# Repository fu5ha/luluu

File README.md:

# LuLuu!

A cute and smart arm-warmer sleeve with a 1.3" full color TFT display built into the back of the
hand ^_^

## Hardware

Runs on a RaspberryPi RP2040 microcontroller. The small 30x75mm PCB has built-in battery management for a single-cell
LiPo, microSD card storage, and direct connection via SPI to an Adafruit 4520 1.3" TFT (ST7789VW controller). It's
also designed to be expanded via SparkFun Qwiic/Adafruit STEMMA QT compatible (3.3v only) I2C sensor modules. Finallly,
it implements the RaspberryPi 3-wire debug connector spec for ARM SWD serial-wire debugging and RS232-style
UART communication.

The hardware design files all live in the [`hardware/`](hardware/) folder. See the [`README`](hardware/README.md) in
that folder for more.

## Software

The firmware that the LuLuu runs is contained in the [`software/`](software/) folder.
It is written in Rust using some of the amazing Rust embedded tooling.
See the [`README`](software/README.md) in that folder for more.

### Installing

You can either install the firmware using the pre-built binary firmware or you can
build it yourself.

#### Pre-built firmware

You can install a pre-built firmware easily via USB by connecting the LuLuu PCB to
your computer via USB, holding the `USBBOOT` button and then pressing the `RESET`
button. This will put the LuLuu into "USB Bootloader mode," causing a "USB storage" 
device to appear on your computer, into which you can drop the compiled `luluu.uf2`
(TODO: link built firmware).

#### Building yourself

To build yourself, see the [`README`](software/README.md) in the
[`software/`](software/) folder.

## Licenses

Hardware is provided under the CERN Open Hardware License 2.0 Permissive variant.

Software is provided under MIT or Apache-2.0 at your choice.

License texts available in the [`licences/`](licenses/) folder.

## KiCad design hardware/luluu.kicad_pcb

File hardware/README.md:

# Hardware

The main part of this folder is the [KiCad](https://www.kicad.org/) project for the main PCB. Open it with KiCad v7+.
There are production files for PCB production and assembly from JLCPCB in the `production/` folder. There is also a
small 3d printed "front panel" part with exported STL files in the `FrontPanel/` folder.

## Online Schematic and Board View

You can view an explorable online version of the schematic and board layout here:
https://kicanvas.org/?github=https%3A%2F%2Fgithub.com%2Ffu5ha%2Fluluu%2Ftree%2Fmain%2Fhardware

## Order and assembly

The board is specifically designed to be economic and easy to order with JLCPCB's
"economic" PCB assembly service. Boards received from JLC will be mostly-assembled
but still require a few pieces of hand assembly: installing the battery connector,
power switch, display connection cable, (optionally) debug connectors, and
(optionally) STEMMAqt connector.

TODO: document BOM, assembly process, etc more

## Front Panel

The front panel part was designed in OnShape. The exported files (printed at JLCPCB in my case but could be printed on
any 3d printer really) can be found in the `FrontPanel/` folder. The original OnShape document can be viewed and
remixed here:

https://cad.onshape.com/documents/f8b0c88e73a74b1a499f2bc3/w/d7cf90c156d1df4edfe95550/e/d6b63c8b8542f003553d2207?renderMode=0&uiState=652e94bf76c80a49126fcdde

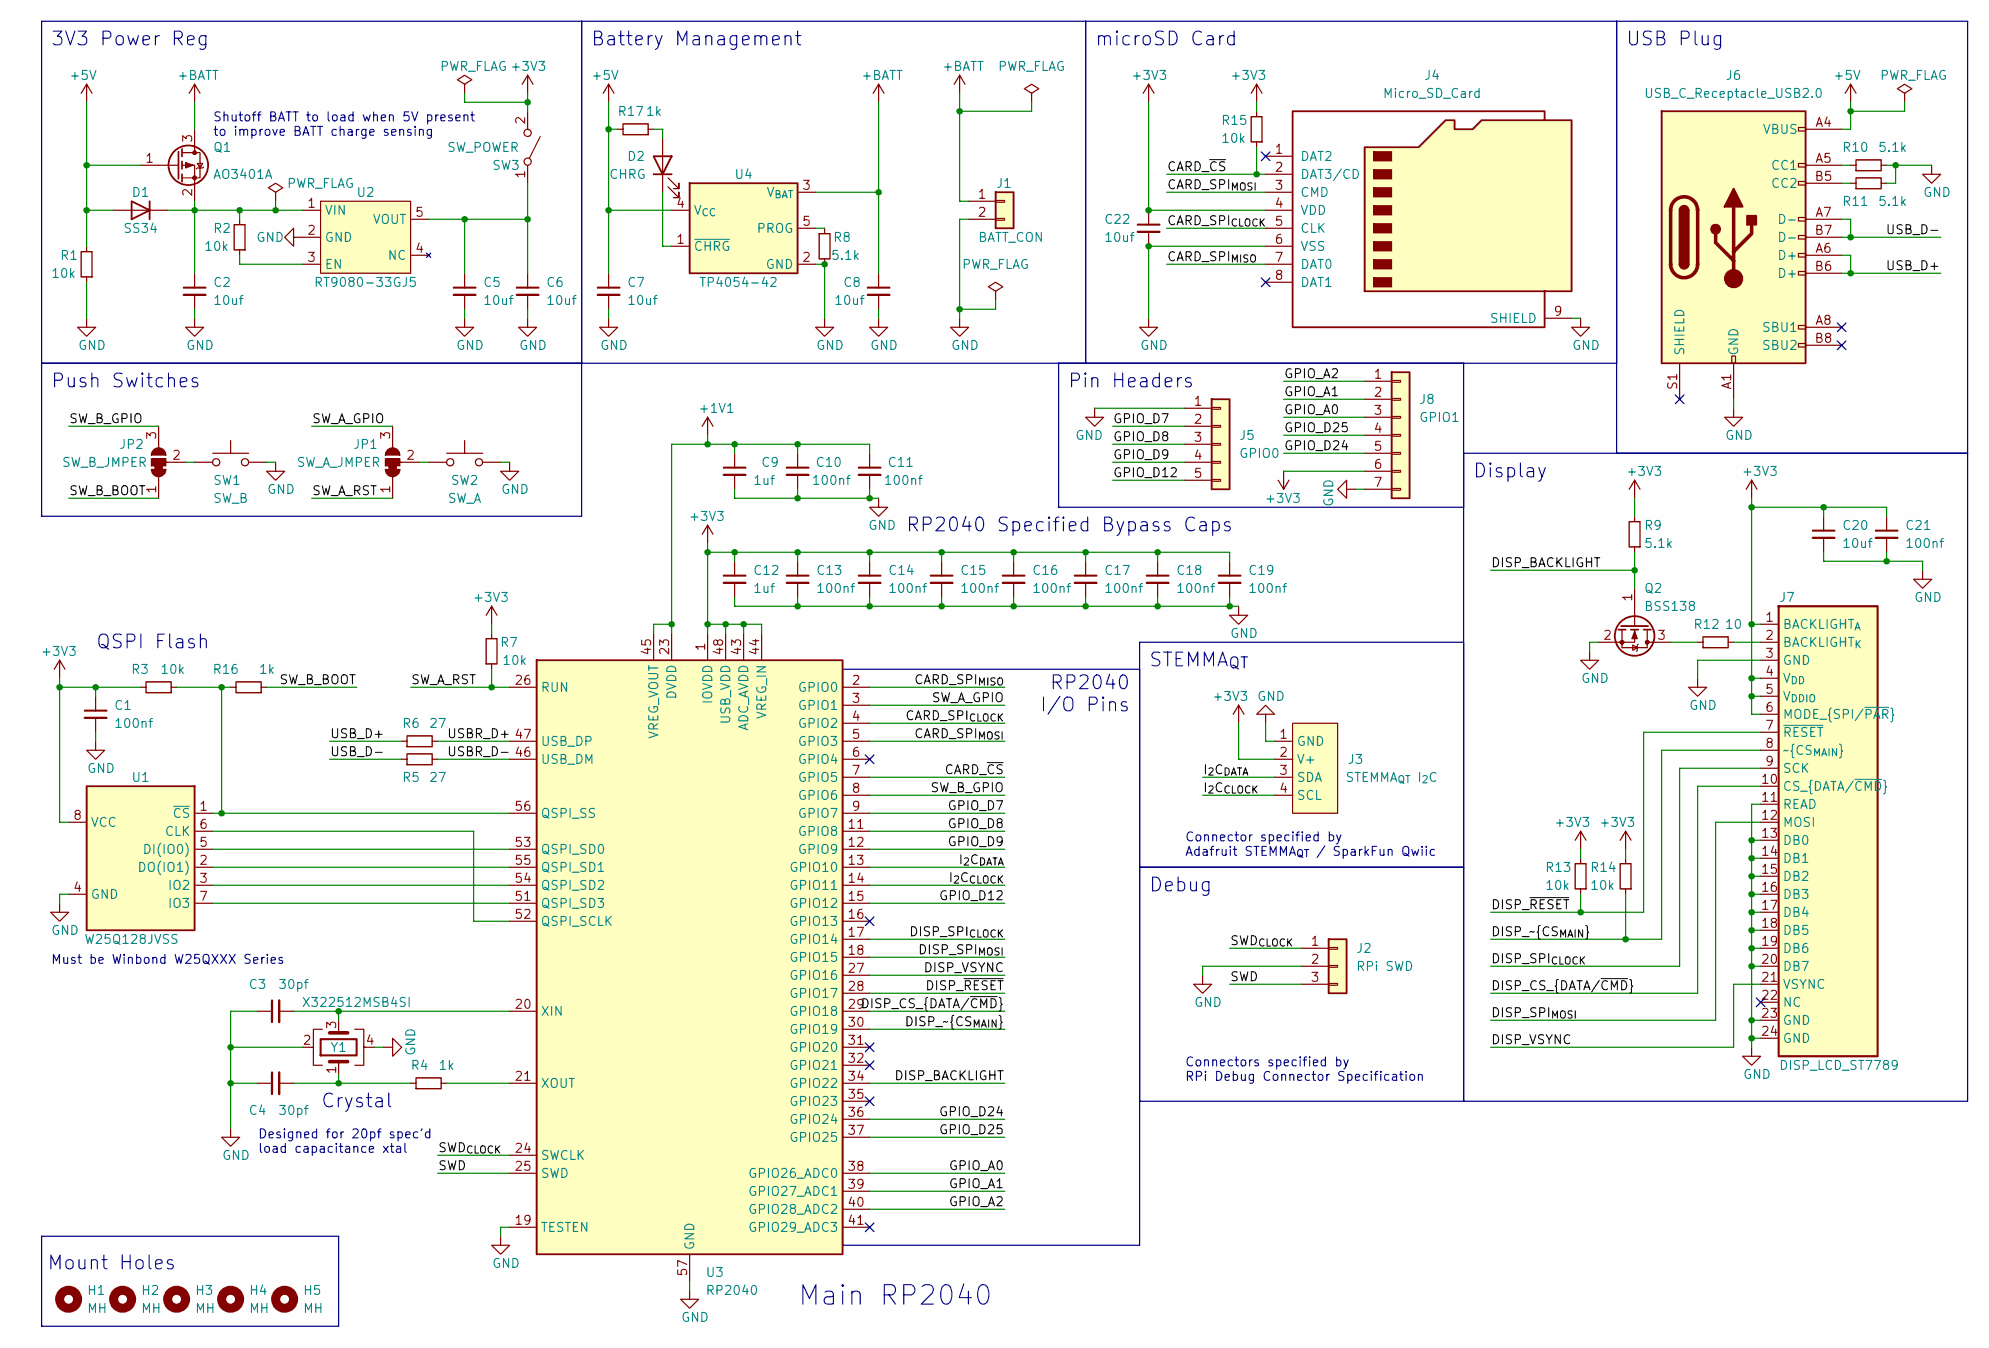
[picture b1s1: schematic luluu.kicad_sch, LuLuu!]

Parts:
C1, C10, C11, C13, C14, C15, C16, C17, C18, C19, C21: 100nf; C_0402_1005Metric_Pad0.74x0.62mm_HandSolder; LCSC C1525
C2, C5, C6, C7, C8, C20, C22: 10uf; C_0603_1608Metric_Pad1.08x0.95mm_HandSolder; LCSC C96446
C3, C4: 30pf; C_0402_1005Metric_Pad0.74x0.62mm_HandSolder; LCSC C1570
C9, C12: 1uf; C_0402_1005Metric_Pad0.74x0.62mm_HandSolder; LCSC C52923
D1: SS34; D_SMA_Handsoldering; LCSC C8678
D2: CHRG; LED_0805_2012Metric_Pad1.15x1.40mm_HandSolder; LCSC C2296
H1, H2, H3, H4, H5: MH; MountingHole_1.1mm_M1
J1: BATT_CON; JST_PH_S2B-PH-SM4-TB_1x02-1MP_P2.00mm_Horizontal; DigiKey 455-S2B-PH-SM4-TBCT-ND
J2: RPi SWD; JST_SH_BM03B-SRSS-TB_1x03-1MP_P1.00mm_Vertical; DigiKey 455-BM03B-SRSS-TBCT-ND
J3: STEMMA_{QT} I_{2}C; JST_SH_SM04B-SRSS-TB_1x04-1MP_P1.00mm_Horizontal; DigiKey 455-SM04B-SRSS-TBCT-ND
J4: Micro_SD_Card; microSD_HC_Molex_104031-0811; LCSC C585350
J5: GPIO0; PinHeader_1x05_P2.54mm_Vertical
J6: USB_C_Receptacle_USB2.0; USB_C_Receptacle_G-Switch_GT-USB-7010ASV; LCSC C2988369
J7: DISP_LCD_ST7789; FPC_24_SOLDER; DigiKey WM11305-ND
J8: GPIO1; PinHeader_1x07_P2.54mm_Vertical
JP1: SW_A_JMPER; SolderJumper-3_P1.3mm_Bridged12_RoundedPad1.0x1.5mm
JP2: SW_B_JMPER; SolderJumper-3_P1.3mm_Bridged12_RoundedPad1.0x1.5mm
Q1: AO3401A; SOT-23; LCSC C15127
Q2: BSS138; SOT-23; LCSC C7420339
R1, R2, R3, R7, R13, R14, R15: 10k; R_0603_1608Metric_Pad0.98x0.95mm_HandSolder; LCSC C25804
R4: 1k; R_0603_1608Metric_Pad0.98x0.95mm_HandSolder; LCSC C21190
R5, R6: 27; R_0603_1608Metric_Pad0.98x0.95mm_HandSolder; LCSC C25190
R8, R9, R10, R11: 5.1k; R_0603_1608Metric_Pad0.98x0.95mm_HandSolder; LCSC C23186
R12: 10; R_0603_1608Metric_Pad0.98x0.95mm_HandSolder; LCSC C22859
R16, R17: 1k; R_0603_1608Metric_Pad0.98x0.95mm_HandSolder; LCSC C25804
SW1: SW_B; SW_Push_1P1T_XKB_TS-1187A; LCSC C318884
SW2: SW_A; SW_Push_1P1T_XKB_TS-1187A; LCSC C318884
SW3: SW_POWER; SW_SPDT_PCM12; DigiKey 401-2016-1-ND
U1: W25Q128JVSS; SOIC-8_5.23x5.23mm_P1.27mm; LCSC C97521
U2: RT9080-33GJ5; SOT-23-5; LCSC C841192
U3: RP2040; QFN-56-1EP_7x7mm_P0.4mm_EP3.2x3.2mm; LCSC C2040
U4: TP4054-42; SOT-23-5; LCSC C32574
Y1: X322512MSB4SI; Crystal_SMD_3225-4Pin_3.2x2.5mm_HandSoldering; LCSC C9002

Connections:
+1V1: C9.1, C10.1, C11.1, U3.23 (DVDD), U3.45 (VREG_VOUT), U3.50 (DVDD)
+3V3: C1.1, C12.1, C13.1, C14.1, C15.1, C16.1, C17.1, C18.1, C19.1, C20.1, C21.1, C22.1, J3.2 (V+), J4.4 (VDD), J7.1 (BACKLIGHT_{A}), J7.4 (V_{DD}), J7.5 (V_{DDIO}), J7.6 (MODE_{SPI/~PAR}), J8.6, R3.2, R7.2, R9.2, R13.2, R14.2, R15.2, SW3.2 (B), U1.8 (VCC), U3.1 (IOVDD), U3.10 (IOVDD), U3.22 (IOVDD), U3.33 (IOVDD), U3.42 (IOVDD), U3.43 (ADC_AVDD), U3.44 (VREG_IN), U3.48 (USB_VDD), U3.49 (IOVDD)
+5V: C7.1, D1.2 (A), J6.A4 (VBUS), J6.A9 (VBUS), J6.B4 (VBUS), J6.B9 (VBUS), Q1.1 (G), R1.2, R17.2, U4.4 (V_{CC})
+BATT: C8.1, J1.1, Q1.3 (D), U4.3 (V_{BAT})
/CARD_SPI_{CLOCK}: J4.5 (CLK), U3.4 (GPIO2)
/CARD_SPI_{MISO}: J4.7 (DAT0), U3.2 (GPIO0)
/CARD_SPI_{MOSI}: J4.3 (CMD), U3.5 (GPIO3)
/CARD_~CS: J4.2 (DAT3/CD), R15.1, U3.7 (GPIO5)
/DISP_BACKLIGHT: Q2.1 (G), R9.1, U3.34 (GPIO22)
/DISP_CS_{DATA/~CMD}: J7.10 (CS_{DATA/~CMD}), U3.29 (GPIO18)
/DISP_SPI_{CLOCK}: J7.9 (SCK), U3.17 (GPIO14)
/DISP_SPI_{MOSI}: J7.12 (MOSI), U3.18 (GPIO15)
/DISP_VSYNC: J7.21 (VSYNC), U3.27 (GPIO16)
/DISP_~CS_{MAIN}: J7.8 (~CS_{MAIN}), R14.1, U3.30 (GPIO19)
/DISP_~RESET: J7.7 (~RESET), R13.1, U3.28 (GPIO17)
/GPIO_A0: J8.3, U3.38 (GPIO26_ADC0)
/GPIO_A1: J8.2, U3.39 (GPIO27_ADC1)
/GPIO_A2: J8.1, U3.40 (GPIO28_ADC2)
/GPIO_D7: J5.2, U3.9 (GPIO7)
/GPIO_D8: J5.3, U3.11 (GPIO8)
/GPIO_D9: J5.4, U3.12 (GPIO9)
/GPIO_D12: J5.5, U3.15 (GPIO12)
/GPIO_D24: J8.5, U3.36 (GPIO24)
/GPIO_D25: J8.4, U3.37 (GPIO25)
/I_{2}C_{CLOCK}: J3.4 (SCL), U3.14 (GPIO11)
/I_{2}C_{DATA}: J3.3 (SDA), U3.13 (GPIO10)
/SWD: J2.3, U3.25 (SWD)
/SWD_{CLOCK}: J2.1, U3.24 (SWCLK)
/SW_A_GPIO: JP1.3 (B), U3.3 (GPIO1)
/SW_A_RST: JP1.1 (A), R7.1, U3.26 (RUN)
/SW_B_BOOT: JP2.1 (A), R16.1
/SW_B_GPIO: JP2.3 (B), U3.8 (GPIO6)
/USBR_D+: R6.2, U3.47 (USB_DP)
/USBR_D-: R5.2, U3.46 (USB_DM)
/USB_D+: J6.A6 (D+), J6.B6 (D+), R6.1
/USB_D-: J6.A7 (D-), J6.B7 (D-), R5.1
GND: C1.2, C2.2, C3.1, C4.1, C5.2, C6.2, C7.2, C8.2, C9.2, C10.2, C11.2, C12.2, C13.2, C14.2, C15.2, C16.2, C17.2, C18.2, C19.2, C20.2, C21.2, C22.2, J1.2, J2.2, J3.1 (GND), J4.6 (VSS), J4.9 (SHIELD), J5.1, J6.A1 (GND), J6.A12 (GND), J6.B1 (GND), J6.B12 (GND), J7.3 (GND), J7.11 (READ), J7.13 (DB0), J7.14 (DB1), J7.15 (DB2), J7.16 (DB3), J7.17 (DB4), J7.18 (DB5), J7.19 (DB6), J7.20 (DB7), J7.23 (GND), J7.24 (GND), J8.7, Q2.2 (S), R1.1, R8.2, R10.2, R11.2, SW1.2, SW2.1, U1.4 (GND), U2.2 (GND), U3.19 (TESTEN), U3.57 (GND), U4.2 (GND), Y1.2, Y1.4
unnamed: C4.2, R4.1, Y1.1
unnamed: C2.1, D1.1 (K), Q1.2 (S), R2.2, U2.1 (VIN)
unnamed: D2.2 (A), R17.1
unnamed: D2.1 (K), U4.1 (~CHRG)
unnamed: J6.A5 (CC1), R10.1
unnamed: J6.B5 (CC2), R11.1
unnamed: J7.2 (BACKLIGHT_{K}), R12.2
unnamed: JP1.2 (C), SW2.2
unnamed: JP2.2 (C), SW1.1
unnamed: Q2.3 (D), R12.1
unnamed: C5.1, C6.1, SW3.1 (A), U2.5 (VOUT)
unnamed: U1.6 (CLK), U3.52 (QSPI_SCLK)
unnamed: U1.5 (DI(IO0)), U3.53 (QSPI_SD0)
unnamed: U1.2 (DO(IO1)), U3.55 (QSPI_SD1)
unnamed: U1.3 (IO2), U3.54 (QSPI_SD2)
unnamed: U1.7 (IO3), U3.51 (QSPI_SD3)
unnamed: R3.1, R16.2, U1.1 (~CS), U3.56 (QSPI_SS)
unnamed: R2.1, U2.3 (EN)
unnamed: C3.2, U3.20 (XIN), Y1.3
unnamed: R4.2, U3.21 (XOUT)
unnamed: R8.1, U4.5 (PROG)

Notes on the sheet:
RP2040 Specified Bypass Caps
QSPI Flash
Pin Headers
Main RP2040
Must be Winbond W25QXXX Series
Push Switches
Mount Holes
Display
RP2040 I/O Pins
USB Plug
Connector specified by Adafruit STEMMA_{QT} / SparkFun Qwiic
Crystal
microSD Card
STEMMA_{QT}
Battery Management
3V3 Power Reg
Connectors specified by RPi Debug Connector Specification
Debug
Designed for 20pf spec'd load capacitance xtal
Shutoff BATT to load when 5V present to improve BATT charge sensing

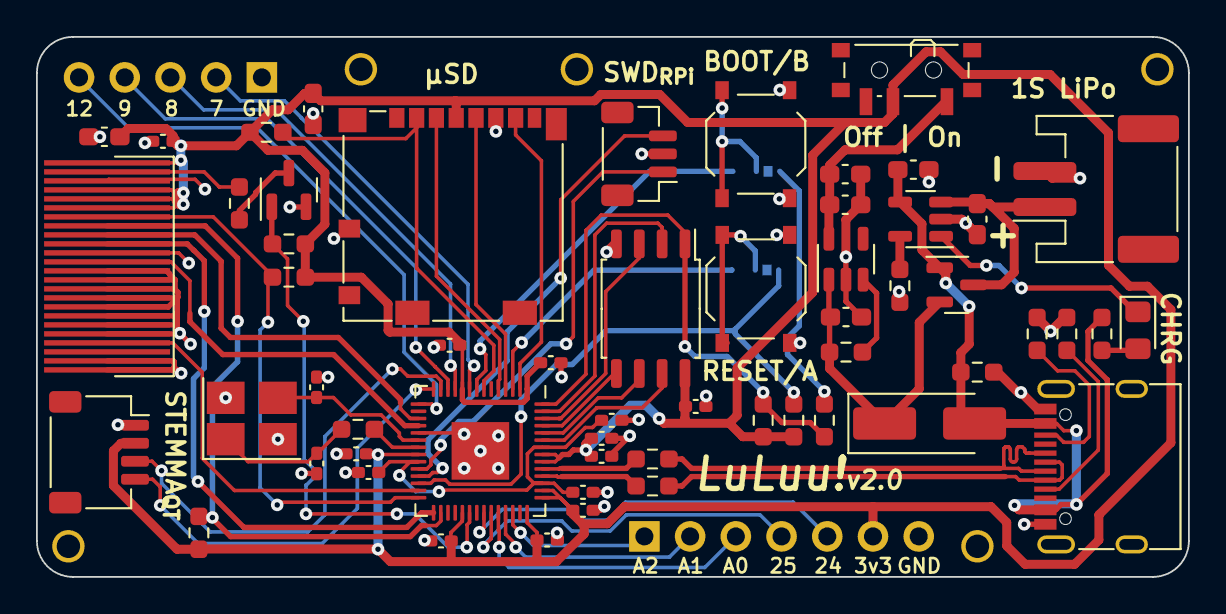
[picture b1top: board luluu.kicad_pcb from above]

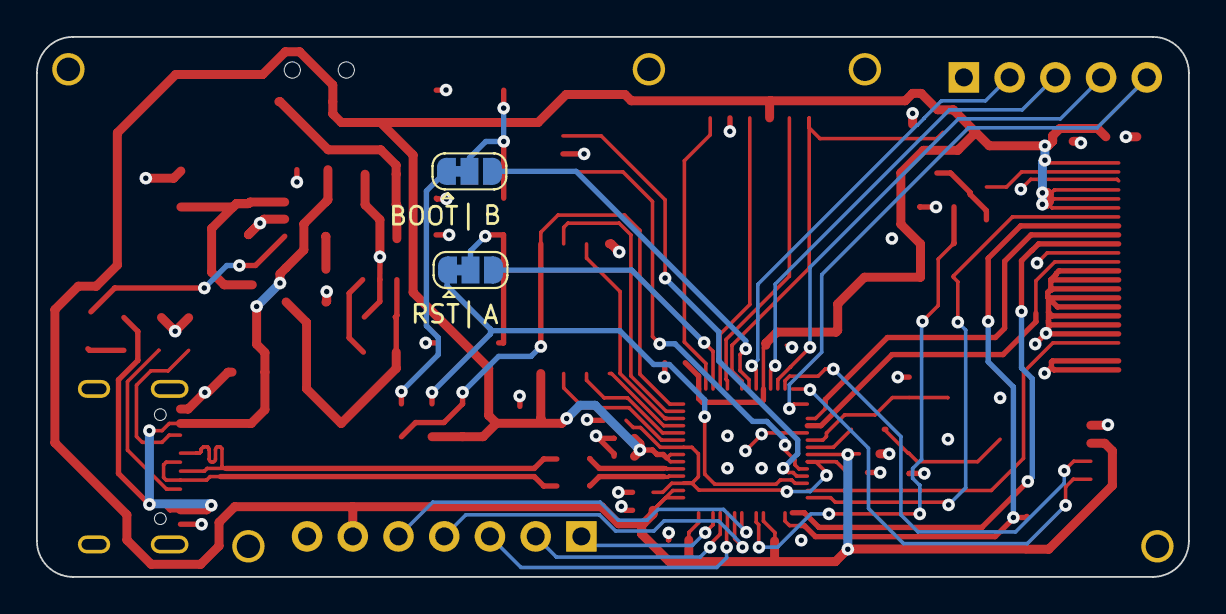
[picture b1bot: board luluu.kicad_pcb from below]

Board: 4 copper layers, 64.0 x 30.0 mm, 66 parts (2 on the bottom side), 58 nets.

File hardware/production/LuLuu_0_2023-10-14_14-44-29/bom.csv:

Designator,Footprint,Quantity,Value,LCSC Part #
"C1, C10, C11, C13, C14, C15, C16, C17, C18, C19, C21",0402,11,100nf,C1525
"C12, C9",0402,2,1uf,C52923
"C2, C20, C22, C5, C6, C7, C8",0603,7,10uf,C96446
"C3, C4",0402,2,30pf,C1570
D1,D_SMA_Handsoldering,1,SS34,C8678
J4,microSD_HC_Molex_104031-0811,1,Micro_SD_Card,C585350
J6,USB_C_Receptacle_G-Switch_GT-USB-7010ASV,1,USB_C_Receptacle_USB2.0,C2988369
Q1,SOT-23,1,AO3401A,C15127
Q2,SOT-23,1,BSS138,C7420339
"R1, R2, R3, R7",0603,4,10k,C25804
"R10, R11, R8, R9",0603,4,5.1k,C23186
R12,0603,1,10,C22859
R4,0603,1,1k,C21190
"R5, R6",0603,2,27,C25190
SW1,SW_Push_1P1T_XKB_TS-1187A,1,SW_USBBOOT,C318884
SW2,SW_Push_1P1T_XKB_TS-1187A,1,SW_RESET,C318884
U1,SOIC-8_5.23x5.23mm_P1.27mm,1,W25Q128JVSS,C97521
U2,SOT-23-5,1,RT9080-33GJ5,C841192
U3,QFN-56-1EP_7x7mm_P0.4mm_EP3.2x3.2mm,1,RP2040,C2040
U4,SOT-23-5,1,TP4054-42,C32574
U5,SOT-23-3,1,APX803S-26/29,C526393
Y1,Crystal_SMD_3225-4Pin_3.2x2.5mm_HandSoldering,1,X322512MSB4SI,C9002

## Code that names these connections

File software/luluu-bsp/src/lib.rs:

#![no_std]

use core::mem::MaybeUninit;

use bytemuck::{NoUninit, Zeroable};
use embedded_sdmmc::{TimeSource, Timestamp};
use hal::rosc::{RingOscillator, Enabled};
use rand_core::RngCore;
pub use rp2040_hal as hal;

#[cfg(feature = "rt")]
use cortex_m_rt as _;
#[cfg(feature = "rt")]
pub use hal::entry;

pub use luluu_enc;

pub use luluu_enc::{Rgb565BE, Rgb565NE, Rgb888};

/// The linker will place this boot block at the start of our program image. We
/// need this to help the ROM bootloader get our code up and running.
#[cfg(feature = "boot2")]
#[link_section = ".boot2"]
#[no_mangle]
#[used]
pub static BOOT2_FIRMWARE: [u8; 256] = rp2040_boot2::BOOT_LOADER_W25Q080;

pub use hal::pac;

use hal::gpio::{Pin, FunctionUart, FunctionI2c, FunctionSpi, FunctionSioInput, FunctionSioOutput, FunctionPwm, PullUp, PullNone, PullDown};
use hal::gpio::bank0::*;

pub type UartTx = Pin<Gpio0, FunctionUart, PullNone>;

pub type UartRx = Pin<Gpio1, FunctionUart, PullNone>;

pub type I2cData = Pin<Gpio2, FunctionI2c, PullUp>;

pub type I2cClock = Pin<Gpio3, FunctionI2c, PullUp>;

pub type SpiMiso = Pin<Gpio8, FunctionSpi, PullDown>;

pub type SpiMosi = Pin<Gpio15, FunctionSpi, PullNone>;

pub type SpiClock = Pin<Gpio14, FunctionSpi, PullNone>;

pub type CardCs = Pin<Gpio5, FunctionSioOutput, PullUp>;

pub type DispVsync = Pin<Gpio16, FunctionSioInput, PullNone>;

pub type DispReset = Pin<Gpio17, FunctionSioOutput, PullNone>;

pub type DispDataCmd = Pin<Gpio18, FunctionSioOutput, PullUp>;

pub type DispCsMain = Pin<Gpio19, FunctionSioOutput, PullUp>;

pub type DispBacklightToggle = Pin<Gpio22, FunctionSioOutput, PullUp>;

pub type DispBacklightPwm = Pin<Gpio22, FunctionPwm, PullUp>;

pub struct Pins {
    /// UART Tx pin
    pub uart_tx: UartTx,

    /// UART Rx pin
    pub uart_rx: UartRx,

    /// I2C Data pin
    pub i2c_data: I2cData,

    /// I2C Clock pin
    pub i2c_clock: I2cClock,

    /// Spi MISO/Rx pin
    pub spi_miso: SpiMiso,

    /// Spi MOSI/Tx pin
    pub spi_mosi: SpiMosi,

    /// Spi Clock pin
    pub spi_clock: SpiClock,

    /// microSD Card chip select (active low) pin
    pub card_cs: CardCs,

    /// Display VSYNC / TE / Tearing Effect pin
    pub disp_vsync: DispVsync,

    /// Display Reset (active low) pin
    pub disp_reset: DispReset,

    /// Display Data (high) / Command (low) (aka RS or DC) pin
    pub disp_data_cmd: DispDataCmd,

    /// Display main chip select (active low) pin
    pub disp_cs_main: DispCsMain,

    /// Display backlight pin.
    ///
    /// Default configured as [`DispBacklightToggle`] but can be reconfigured as [`DispBacklightPwm`]:
    ///
    /// ```ignore
    /// let bl_pin: DispBacklightPwm = pins.disp_backlight.reconfigure();
    /// ```
    pub disp_backlight: DispBacklightToggle,
}

impl Pins {
    pub fn new(
        io: hal::pac::IO_BANK0,
        pads: hal::pac::PADS_BANK0,
        sio: hal::sio::SioGpioBank0,
        reset: &mut hal::pac::RESETS,
    ) -> Self {
        let pins = hal::gpio::Pins::new(io, pads, sio, reset);
        Self {
            uart_tx: pins.gpio0.reconfigure(),
            uart_rx: pins.gpio1.reconfigure(),
            i2c_data: pins.gpio2.reconfigure(),
            i2c_clock: pins.gpio3.reconfigure(),
            spi_miso: pins.gpio8.reconfigure(),
            spi_mosi: pins.gpio15.reconfigure(),
            spi_clock: pins.gpio14.reconfigure(),
            card_cs: pins.gpio5.reconfigure(),
            disp_vsync: pins.gpio16.reconfigure(),
            disp_reset: pins.gpio17.reconfigure(),
            disp_data_cmd: pins.gpio18.reconfigure(),
            disp_cs_main: pins.gpio19.reconfigure(),
            disp_backlight: pins.gpio22.reconfigure(),
        }
    }
}

/// Layout of Spi pins.
pub type SpiPinLayout = (SpiMosi, SpiMiso, SpiClock);

/// A dummy timesource, which is mostly important for creating files. Since we have no real-time
/// clock, just dummy it to the beginning of 2023.
#[derive(Default)]
pub struct DummyTimesource;

impl TimeSource for DummyTimesource {
    fn get_timestamp(&self) -> Timestamp {
        Timestamp {
            year_since_1970: 53,
            zero_indexed_month: 0,
            zero_indexed_day: 0,
            hours: 0,
            minutes: 0,
            seconds: 0,
        }
    }
}

#[macro_export]
macro_rules! singleton {
    {
        $name:ident {
            $(#[$staticattr:meta])*
            static mut $staticname:ident: $t:ty = $initializer:expr;
        }
    } => {
        $(#[$staticattr])*
        static mut $staticname: $t = $initializer;
        struct $name(&'static mut $t);

        impl Deref for $name {
            type Target = $t;

            #[inline(always)]
            fn deref(&self) -> &Self::Target {
                self.0
            }
        }

        impl DerefMut for $name {
            #[inline(always)]
            fn deref_mut(&mut self) -> &mut Self::Target {
                self.0
            }
        }

        impl $name {
            pub unsafe fn acquire() -> Self {
                Self(unsafe { &mut $staticname })
            }
        }
    };
}

/// Generate a random u32
pub fn gen_rand_u32(rosc: &mut RingOscillator<Enabled>) -> u32 {
    RngCore::next_u32(rosc)
}

/// Crystal oscillator frequency, 12Mhz is expected by the RP2040 and it's what ours is.
pub const XOSC_CRYSTAL_FREQ: u32 = 12_000_000;

/// Crystal oscillator stability delay. Depends on crystal properties, 100ms seems to be
/// required for our crystal.
pub const XOSC_STABLE_DELAY_MILLIS: u32 = 100;

/// The number of pixels in a full-size framebuffer
pub const FULL_FRAMEBUFFER_SIZE: usize = 240 * 240;

/// The number of pixels in a half-size framebuffer
pub const HALF_FRAMEBUFFER_SIZE: usize = 120 * 120;

#[derive(Clone, Copy)]
#[repr(transparent)]
pub struct Framebuffer<P, const N: usize = FULL_FRAMEBUFFER_SIZE> {
    data: [P; N],
}

impl<P: Clone + Copy, const N: usize> Framebuffer<P, N> {
    pub const fn const_new(initial: P) -> Self {
        Self { data: [initial; N] }
    }
}

impl<P: Zeroable, const N: usize> Framebuffer<P, N> {
    pub fn new() -> Self {
        // SAFETY: P is zeroable
        Self { data: unsafe { <MaybeUninit<[P; N]>>::zeroed().assume_init() } }
    }
}

impl<P: NoUninit, const N: usize> Framebuffer<P, N> {
    pub fn as_bytes(&self) -> &[u8] {
        // SAFETY: P has no uninit and is tightly packed
        unsafe {
            core::slice::from_raw_parts(
                self.data.as_ptr().cast(),
                self.data.len() * core::mem::size_of::<P>()
            )
        }
    }
}

impl<P, const N: usize> Framebuffer<P, N> {
    #[inline(always)]
    pub const fn pixels(&self) -> &[P; N] {
        &self.data
    }

    #[inline(always)]
    pub fn pixels_mut(&mut self) -> &mut [P; N] {
        &mut self.data
    }
}

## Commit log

2023-10-11 initial
2023-10-12 fix usb cc resistor
2023-10-12 re-annotate, add display decoupling caps
2023-10-12 lots of updates
2023-10-13 update footprints and sourcing
2023-10-13 remove unnecessary symbol fields
2023-10-13 tiny schematic cleanup
2023-10-13 design rules
2023-10-14 initial routing, various fixes
2023-10-14 exclusions, tiny fix
2023-10-14 update pwr switch silkscreen
2023-10-16 initial prod
2023-10-16 layout improvements and jlcpcb part positioning offsets
2023-10-16 remove lockfiles
2023-10-16 final_prod
2023-10-17 add pullups to disp reset, disp csmain, card cs
2023-10-17 rev1
2023-10-17 Add front panel part
2023-10-17 update front panel stls
2023-10-17 improve readmes
2023-10-17 fix img links
2023-10-17 add link to schematic from hardware readme
2023-10-17 licenses, initial software stub
2023-10-17 change from farnell to digikey for other bom parts
2023-10-18 software bashing
2023-11-01 more software bashing; vendor it
2023-11-02 rev1.1 - fix USB data and 1k boot resistor
2023-11-02 basic display functionality
2023-11-14 live read from sd card to display
2023-11-14 optimize read and blit loop, setup no probe build
2023-11-15 use longer xtal startup delay to fix unstable boot
2023-11-15 random config
2023-11-15 Reconfigurations and small improvements
2023-11-15 experimentation with frame rates and sizes
2023-11-17 start on rev2 of pcb
2023-11-21 pcb rev 2.0 progress
2023-11-21 more work on v2.0
2023-11-22 optimize usb routing
2023-11-23 more work on v2
2023-11-28 2.0 release candidate
